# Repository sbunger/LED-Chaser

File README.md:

# LED-Chaser
A simple LED chaser board using a 555 IC. Ten LEDs will blink in sequence. I created a custom PCB in KICAD, based on a ten-pointed flower design. I created this by following the hackclub tutorial at this link: <a href="https://blueprint.hackclub.com/starter-projects/blinky">https://blueprint.hackclub.com/starter-projects/blinky</a>. All custom design was created in affinity designer. The board is powered by an external battery with pin connectors.

This project is one of my first hardware projects without a microcontroller, and I created it to improve my KICAD skills and gain more experience soldering, as all the parts are through-hole components. I hope that the soldering process goes smoothly!

## Schematic

## PCB

## 3D View

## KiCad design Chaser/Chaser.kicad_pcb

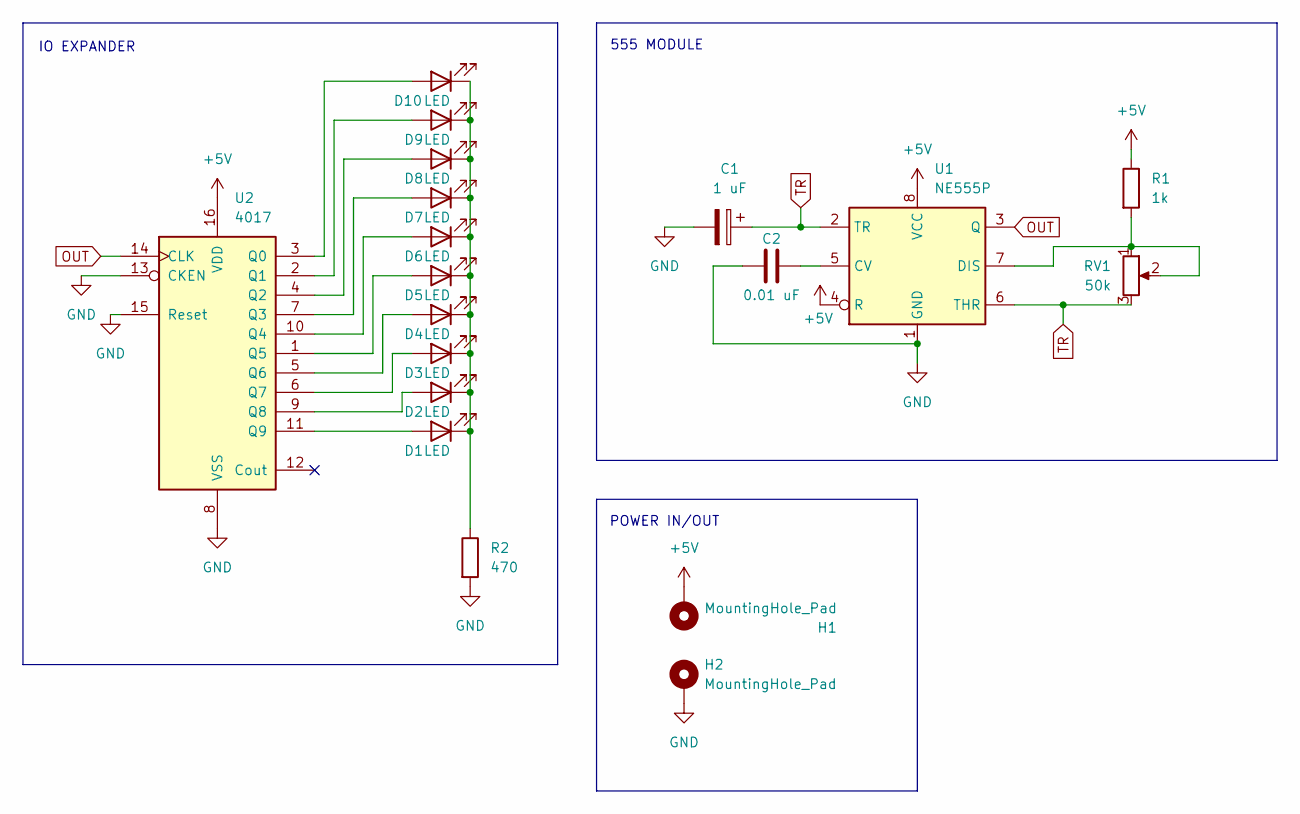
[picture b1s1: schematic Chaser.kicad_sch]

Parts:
C1: 1 uF; CP_Radial_D5.0mm_P2.00mm
C2: 0.01 uF; CP_Radial_D5.0mm_P2.00mm
D1, D2, D3, D4, D5, D6, D7, D8, D9, D10: LED; LED_D3.0mm
H1, H2: MountingHole_Pad; PinSocket_1x01_P2.54mm_Vertical
R1: 1k; R_Axial_DIN0207_L6.3mm_D2.5mm_P7.62mm_Horizontal
R2: 470; R_Axial_DIN0207_L6.3mm_D2.5mm_P7.62mm_Horizontal
RV1: 50k; R_Axial_DIN0207_L6.3mm_D2.5mm_P7.62mm_Horizontal
U1: NE555P; DIP-8_W7.62mm
U2: 4017; N16

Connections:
+5V: H1.1, R1.1, U1.4 (R), U1.8 (VCC), U2.16 (VDD)
GND: C1.2, C2.1, H2.1, R2.2, U1.1 (GND), U2.8 (VSS), U2.13 (CKEN), U2.15 (Reset)
unnamed: D1.2 (A), U2.11 (Q9)
unnamed: D1.1 (K), D2.1 (K), D3.1 (K), D4.1 (K), D5.1 (K), D6.1 (K), D7.1 (K), D8.1 (K), D9.1 (K), D10.1 (K), R2.1
unnamed: D2.2 (A), U2.9 (Q8)
unnamed: D3.2 (A), U2.6 (Q7)
unnamed: D4.2 (A), U2.5 (Q6)
unnamed: D5.2 (A), U2.1 (Q5)
unnamed: D6.2 (A), U2.10 (Q4)
unnamed: D7.2 (A), U2.7 (Q3)
unnamed: D8.2 (A), U2.4 (Q2)
unnamed: D9.2 (A), U2.2 (Q1)
unnamed: D10.2 (A), U2.3 (Q0)
unnamed: C2.2, U1.5 (CV)
unnamed: R1.2, RV1.1, RV1.2, U1.7 (DIS)
OUT: U1.3 (Q), U2.14 (CLK)
TR: C1.1, RV1.3, U1.2 (TR), U1.6 (THR)

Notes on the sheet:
POWER IN/OUT
555 MODULE
IO EXPANDER

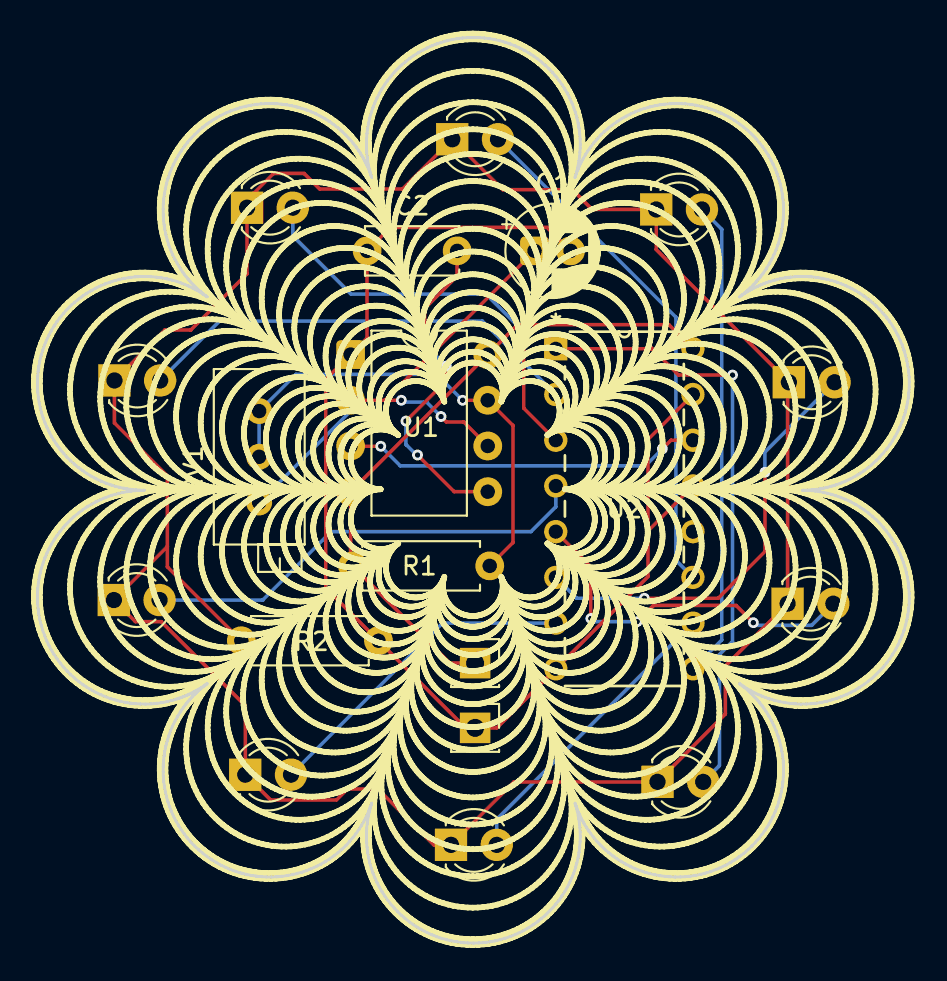
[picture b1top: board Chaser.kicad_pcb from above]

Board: 2 copper layers, 48.4 x 50.3 mm, 19 parts (0 on the bottom side), 17 nets.

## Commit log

2026-01-04 all files added
2026-01-04 Enhance README with project details and images
    Expanded project description with details about PCB design, tutorial reference, and soldering experience.
2026-01-04 fixed footprints
2026-01-04 clean up repository structure, last minute pcb silkscreen fix
2026-01-04 Fix image paths in README for consistency
    Updated image paths in README to use correct casing.
